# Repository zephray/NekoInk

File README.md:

NekoInk
=======

**This project has been superseded by [Glider](https://gitlab.com/zephray/glider) and will not be updated further.**

NekoInk is an open-source, programmable, and versatile E-paper display platform. It offers connectivity options to various type of E-paper screens, and flexible programming environment choices.

# Hardware

## Mainboard

The 1st generation of NekoInk has the following specs:

* Processing
    - NXP i.MX6ULL, 900 MHz Cortex-A7 processor
    - 512 MB DDR3L-1066 memory
* Display
    - Support for EPD screens from 6" to 13.3"
    - Up to 32 greyscale levels / 32768 colors (depends on screen)
    - 40 pin connector for ED103TC1/ES103TC2/GDEW101C01
    - 6 and 12 pin connector for capacitive touch screen (shared signal)
    - 30 pin connector for LVDS LCDs
* Connectivity
    - MicroSD slot for storage
    - 1x USB Micro-B for USB Device and charging
    - 1x USB Micro-AB for USB Host
    - 1x USB Micro-B for USB Serial terminal
    - 1x DVP port for HDMI input or camera module
    - Integrated WiFi and Bluetooth
* Power
    - AXP209 PMIC with Lithium battery charger and coulomb counter
    - Power consumption T.B.D.

## Screen Adapter

Adapter boards are available in this repo to adapt the following screens:

* 39 pin connector for ED060SC4/ED133UT2
* 34 pin connector for ED060SCF/SCN/SCP/XC3/XC5/XC9/XD4/XD6/XH2/KC1/KD1
* 35 pin connector for ED060XC8/TC1
* 50 pin connector for ES108FC1

It's possible to use a simple FPC extender to support the following screens:

* ED078KC1/KH4/GDEW078M01/078C01

The hardware is designed with KiCAD 7.0.

## Status

The 1st gen mainboard is finished, soldered, and tested and considered stable. However there is no plan for mass-production.

# Software

T.B.D.

## Operating System

Linux T.B.D.

## Waveform

This project uses a human-readable waveform format (iwf, Interchangable Waveform Format) described below. Currently this could be converted into .fw format used by i.MX6/7 EPDC/EPDCv2. Converting from Eink's wbf format is also supported.

### Waveform Format

The waveform consists of one descriptor file in iwf extension (ini format) and various lut data files in csv format.

The descriptor contains the follwoing required fields:

* VERISON: the version of the descriptor
* NAME: (optional) original name for the waveform
* BPP: (optional, default 4) 4 or 5, representing the internal state count used for waveform
* PREFIX: the filename prefix for actual waveform files
* MODES: the total modes supported by the waveform
* TEMPS: the total number of temperature ranges supported by the waveform
* T*x*RANGE: the supported temperature in degC, where x is the temperature ID
* TUPBOUND: (optional) upper bound for temperature range, each range is T*x*RANGE to T*x+1*RANGE (or TUPBOUND in case of the last one)

In v2.0, the following fields are added:

* TABLES: total number of LUTs inside the waveform
* TB*x*FC: the frame count for the table, where x is the table ID

In v1.0, table are directly addressed and stored by its mode and temperature ID (expect things like PREFIX_M1_T2.csv for mode 1 and temperature range 2). In v2.0, tables are indirectly addressed and stored (expect things like PREFIX_TB2.csv for the second table, and one or more mode/temperature combination to use/ reference table 2).

Each mode has its own mode section named \[MODE*x*\], where x is the mode ID, containing the following fields:

* NAME: the name for that mode
* TxFC: the frame count for the temperature in that mode, where x is the temperature ID (v1.0 only)
* T*TABLE: the table used for the temperature in that mode (v2.0 only)

There should be a number of LUTs, saved in the filename of either PREFIX_M*x*_T*y*.csv (v1.0) or PREFIX_TB*x*.csv. Each csv file should contain the a LUT like this: lut\[src\]\[dst\]\[frame\], which means, to transition from src greyscale level to dst greyscale level, at a certain frame in a frame sequence, what voltage should be applied to the screen (0/3: GND / Keep, 1: VNEG / To black, 2: VPOS / To white). Each line contains the frame sequence for one or more source to destination pairs.

For example:

* ```4,7,1,1,1,0,2``` means to transition from greyscale level 4 to greyscale level 7, there should be 5 frames, each applying VNEG VNEG VNEG GND VPOS
* ```0:14:15,2,2,2``` means to transition from any greyscale level from 0 to 14 to greyscale level 15, there should be 3 frames, each applying VPOS VPOS VPOS

These are provided to only illustrate the file format, they are not valid or meaningful Eink driving sequences.

With current design, each mode should have fixed frame count for all associated frame sequences.

### Converting

Tools are provided in utils/ folder.

* To convert from iwf to fw (iMX6/7 EPDC format): ```./mxc_wvfm_asm v1/v2 input.iwf output.fw``` 
* To convert from fw to iwf: ```./mxc_wvfm_dump v1/v2 input.fw output_prefix```
* To convert from wbf to iwf: ```./wbf_wvfm_dump input.wbf output_prefix```

In some cases, the waveform stored on the panel/ controller's flash is compressed. A decompressing tool is also provided that might work.

### Generating

To be implemented.

# License

The design, unless otherwise specified, is released under the CERN Open Source Hardware License version 2 permissive variant, CERN-OHL-P. A copy of the license is provided in the source repository. Additionally, user guide of the license is provided on ohwr.org.

The waveform converting tool is licensed under GNU GPLv2+ due to use of Linux kernel source code and other people's valuable prior work. See each tools' source code for the complete copyright.

The image viewer tool is licensed under MIT. stb library used in the image viewer is public domain.

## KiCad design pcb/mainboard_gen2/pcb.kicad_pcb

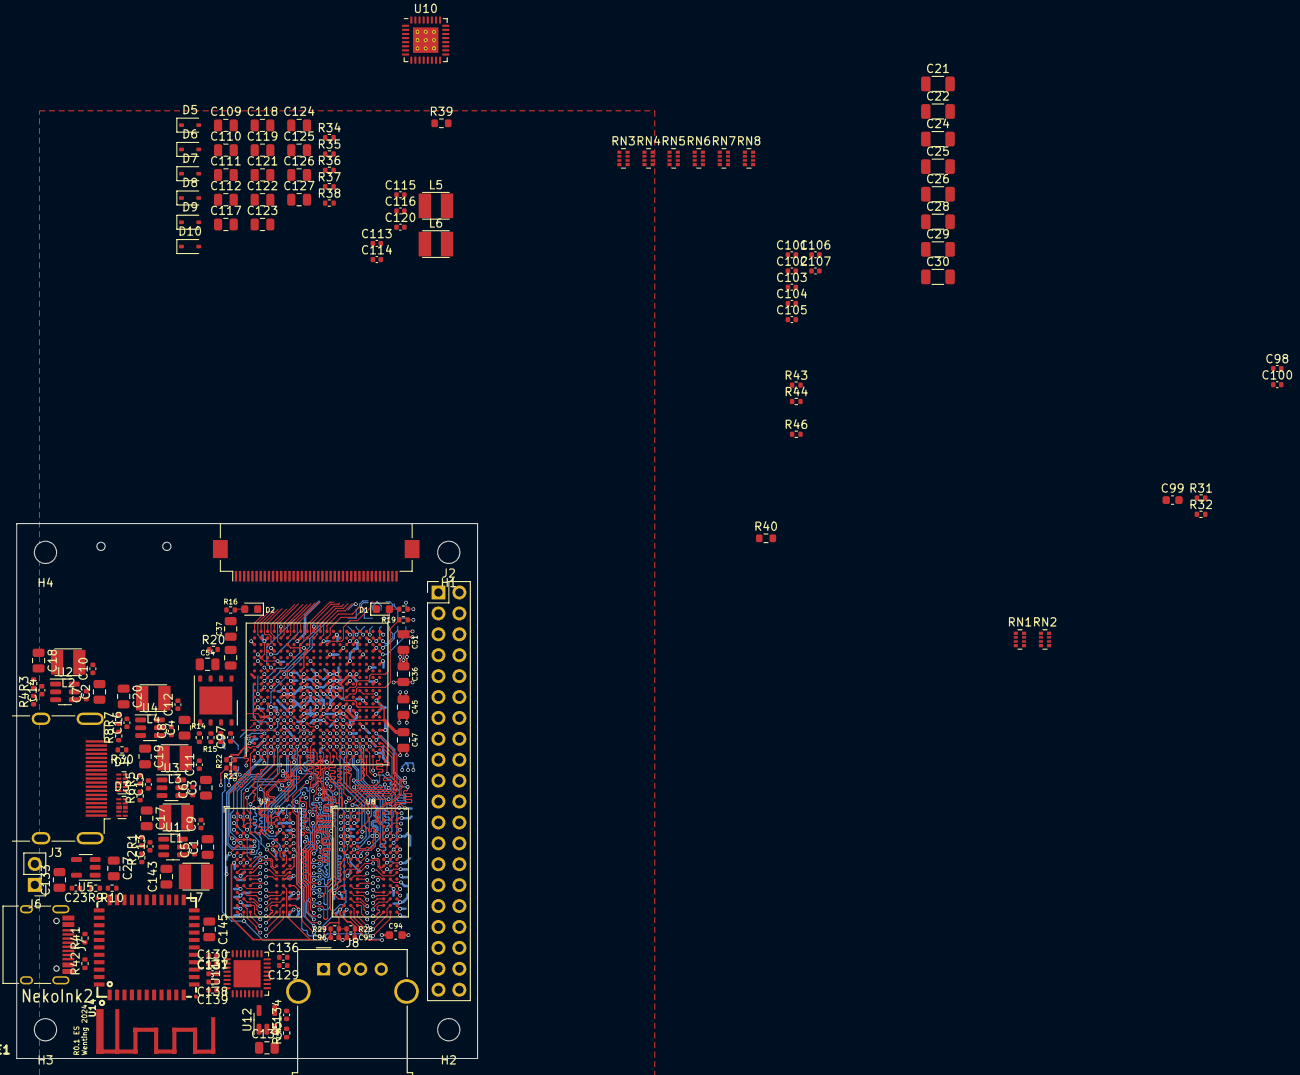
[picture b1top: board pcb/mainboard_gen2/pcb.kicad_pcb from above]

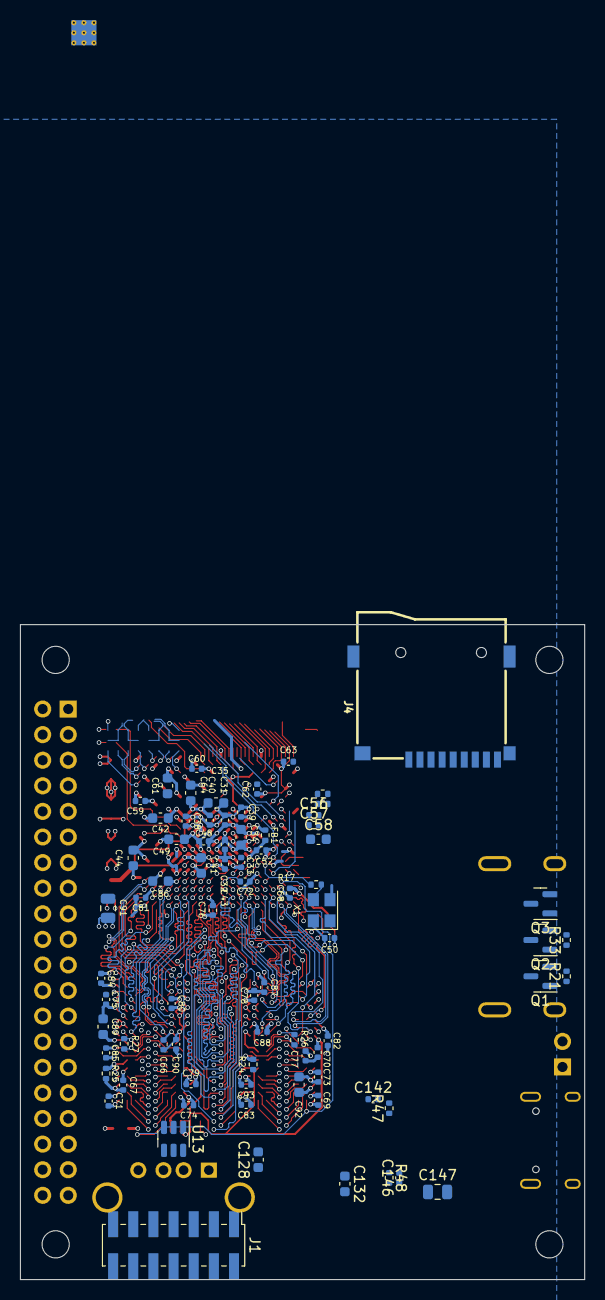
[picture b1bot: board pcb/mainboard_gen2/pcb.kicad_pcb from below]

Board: 6 copper layers, 56.0 x 65.0 mm, 245 parts (77 on the bottom side), 245 nets.

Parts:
AE1: Antenna_Shield; bt_antenna_1ant_2gnd_mirror
C1, C2, C3, C4, C17, C18, C19, C20, C27, C119, C125, C133, C135, C143, C145, C147: 10uF; C_0805_2012Metric
C5, C6, C7, C8, C9, C10, C11, C12, C23, C67, C70, C95, C96, C100, C113, C114, C115, C129, C130, C131, C134, C136, C137, C138, C139, C142, C146: 100nF; C_0402_1005Metric
C13, C14, C15, C16: 47pF; C_0402_1005Metric
C21, C22, C24, C25, C26, C28, C29, C30: 47uF/10V; C_1206_3216Metric
C31, C32, C33, C38, C39, C40, C43, C48, C50, C52, C56, C57, C59, C60, C62, C63, C68, C72, C76, C81, C97: 470nF; C_0402_1005Metric
C34, C35, C41, C42, C44, C49, C58, C61, C64, C86, C94, C128, C132: 4.7uF; C_0603_1608Metric
C36, C37, C45, C46, C47, C51: 100uF; C_0805_2012Metric
C54, C91: 47uF; C_0805_2012Metric
C66, C69, C71, C73, C74, C75, C77, C78, C79, C80, C82, C83, C84, C85, C87, C88, C90, C93, C101, C102, C103, C104, C105, C106, C107: 220nF; C_0402_1005Metric
C89, C92, C99: 22uF; C_0603_1608Metric
C98: 18pF; C_0402_1005Metric
C109, C110, C111, C112: 1uF/25V; C_0805_2012Metric
C116: 1uF; C_0402_1005Metric
C117, C118, C121, C122, C123, C124, C126, C127: 4.7uF/25V; C_0805_2012Metric
C120: 2.2nF; C_0402_1005Metric
D1, D2: LED; LED_0603_1608Metric
D3, D4: RCLAMP0524P; Diodes_UDFN-10_1.0x2.5mm_P0.5mm
D5, D6, D7, D8, D9, D10: B0530WS; D_SOD-323
FB1: 120R; R_0402_1005Metric
H1, H2, H3, H4: MountingHole; MountingHole_2.7mm_M2.5
J1: JTAG; PinHeader_2x07_P2.00mm_Vertical_SMD
J2: GPIO; PinHeader_2x20_P2.54mm_Vertical
J3: HDMI_A; HDMI_A_Molex_208658-1001_Horizontal
J4: MICRO_SD(TFC-WPAPR-08); TFC-WPAPR-08
J5: 0.5mm; Hirose_FH12-40S-0.5SH_1x40-1MP_P0.50mm_Horizontal_Reversed
J6: Conn_01x02; PinHeader_1x02_P2.54mm_Vertical
J7: USB_C_Receptacle_USB2.0; USB_C_Receptacle_HRO_TYPE-C-31-M-12
J8: USB_A; USB_A_Molex_67643_Horizontal
L1, L2, L3, L4, L5, L6, L7: 4.7uH; L_1212
Q1, Q2, Q3: BSS138; SOT-23
R1: 91K/1%; R_0402_1005Metric
R2, R3, R5: 20K/1%; R_0402_1005Metric
R4: 10K/1%; R_0402_1005Metric
R6, R7: 16K/1%; R_0402_1005Metric
R8, R36: 27K/1%; R_0402_1005Metric
R9, R19: 4.7K; R_0402_1005Metric
R10: 16K; R_0402_1005Metric
R11, R12, R13, R14, R15, R31: 20K; R_0402_1005Metric
R16, R18, R30, R46: 1K; R_0402_1005Metric
R17, R32, R43, R47, R48: 22R; R_0402_1005Metric
R20, R21, R33, R41, R42, R45: 10K; R_0402_1005Metric
R22, R23: 80R; R_0402_1005Metric
R24, R25: 240R 1%; R_0402_1005Metric
R26, R27: 100R; R_0402_1005Metric
R28, R29: 1.5K/0.5%; R_0402_1005Metric
R34: 562K/1%; R_0402_1005Metric
R35: 806K/1%; R_0402_1005Metric
R37: 49.9K/1%; R_0402_1005Metric
R38: 10R; R_0402_1005Metric
R39: 0.5R; R_0603_1608Metric
R40: 22R; R_0603_1608Metric
R44: 12K/1%; R_0402_1005Metric
RN1, RN2: 51; R_Array_Convex_4x0402
RN3, RN4, RN5, RN6, RN7, RN8: 33; R_Array_Convex_4x0402
U1, U2, U3, U4: SY8120; TSOT-23-6
U5, U12: MT9700; SOT-23-5
U6: XC7Z010-CLG400; Xilinx_CLG400
U7, U8: MT41K256M16HA; BGA-96_9.0x13.0mm_Layout2x3x16_P0.8mm
U9: W25Q128JVP; WSON-8-1EP_6x5mm_P1.27mm_EP3.4x4mm
U10: MAX17135; QFN-32-1EP_5x5mm_P0.5mm_EP3.1x3.1mm_ThermalVias
U11: USB3300; QFN-32-1EP_5x5mm_P0.5mm_EP3.3x3.3mm
U13: USBLC6-2SC6; SOT-23-6
U14: AP6330(BCM4330); RL-SM02BD(RTL8723BS)
X1: 33.33MHz; Oscillator_SMD_Abracon_ASE-4Pin_3.2x2.5mm

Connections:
+1V0: C16.2, C20.2, C31.1, C33.1, C35.1, C37.1, C38.1, C39.1, C40.1, C41.1, C42.1, C46.1, C47.1, L4.2, R7.2, U6.G7 (VCCPINT[6]), U6.G11 (VCCBRAM[2]), U6.G13 (VCCINT[9]), U6.H10 (VCCBRAM[2]), U6.H12 (VCCINT[9]), U6.J7 (VCCPINT[6]), U6.J13 (VCCINT[9]), U6.K12 (VCCINT[9]), U6.L7 (VCCPINT[6]), U6.L13 (VCCINT[9]), U6.M12 (VCCINT[9]), U6.N7 (VCCPINT[6]), U6.N13 (VCCINT[9]), U6.P8 (VCCPINT[6]), U6.P12 (VCCINT[9]), U6.R7 (VCCPINT[6]), U6.R13 (VCCINT[9])
+1V8: C14.2, C18.2, C32.1, C34.1, C36.1, C48.1, C49.1, C51.1, C59.1, C60.1, C61.1, FB1.2, L2.2, R3.2, U6.F8 (VCCPAUX[5]), U6.F11 (VCCBATT_0), U6.G9 (VCCPAUX[5]), U6.H8 (VCCPAUX[5]), U6.J9 (VCCADC_0), U6.J11 (VCCAUX[6]), U6.K8 (VCCPAUX[5]), U6.L11 (VCCAUX[6]), U6.M8 (VCCPAUX[5]), U6.N9 (VCCAUX[6]), U6.N11 (VCCAUX[6]), U6.N19 (VCCO_34[6]), U6.P10 (VCCAUX[6]), U6.R9 (VCCAUX[6]), U6.R15 (VCCO_34[6]), U6.T18 (VCCO_34[6]), U6.V14 (VCCO_34[6]), U6.W17 (VCCO_34[6]), U6.Y20 (VCCO_34[6])
+1V35: C15.2, C19.2, C66.1, C68.1, C69.1, C71.1, C72.1, C73.1, C74.1, C75.1, C76.1, C77.1, C78.1, C79.1, C80.1, C81.1, C82.1, C83.1, C84.1, C85.1, C86.1, C87.1, C88.1, C89.1, C90.1, C91.1, C92.1, C93.1, C94.1, C95.1, L3.2, R5.2, R22.1, R28.1, U6.A3 (VCCO_DDR_502[10]), U6.D2 (VCCO_DDR_502[10]), U6.E5 (VCCO_DDR_502[10]), U6.G1 (VCCO_DDR_502[10]), U6.H4 (VCCO_DDR_502[10]), U6.L3 (VCCO_DDR_502[10]), U6.P2 (VCCO_DDR_502[10]), U6.R5 (VCCO_DDR_502[10]), U6.U1 (VCCO_DDR_502[10]), U6.V4 (VCCO_DDR_502[10]), U7.A1 (VDDQ), U7.A8 (VDDQ), U7.B2 (VDD), U7.C1 (VDDQ), U7.C9 (VDDQ), U7.D2 (VDDQ), U7.D9 (VDD), U7.E9 (VDDQ), U7.F1 (VDDQ), U7.G7 (VDD), U7.H2 (VDDQ), U7.H9 (VDDQ), U7.K2 (VDD), U7.K8 (VDD), U7.N1 (VDD), U7.N9 (VDD), U7.R1 (VDD), U7.R9 (VDD), U8.A1 (VDDQ), U8.A8 (VDDQ), U8.B2 (VDD), U8.C1 (VDDQ), U8.C9 (VDDQ), U8.D2 (VDDQ), U8.D9 (VDD), U8.E9 (VDDQ), U8.F1 (VDDQ), U8.G7 (VDD), U8.H2 (VDDQ), U8.H9 (VDDQ), U8.K2 (VDD), U8.K8 (VDD), U8.N1 (VDD), U8.N9 (VDD), U8.R1 (VDD), U8.R9 (VDD)
+3V3: C13.2, C17.2, C43.2, C44.2, C45.2, C50.2, C56.1, C57.1, C58.1, C62.1, C63.1, C64.1, C97.2, C99.1, C100.1, C105.1, C136.1, C137.1, C138.1, C139.1, C142.1, C145.1, C146.1, C147.1, J1.2, J2.1, J2.17, J4.4 (VDD), J5.5, J5.11, L1.2, Q1.1 (G), Q2.1 (G), Q3.1 (G), R1.2, R11.1, R14.1, R18.1, R19.1, R20.1, R21.1, R31.1, R33.1, RN1.1 (R1.1), RN1.2 (R2.1), RN1.3 (R3.1), RN1.4 (R4.1), RN2.1 (R1.1), RN2.2 (R2.1), RN2.3 (R3.1), RN2.4 (R4.1), U6.A13 (VCCO_MIO1_501[4]), U6.B6 (VCCO_MIO0_500[2]), U6.B16 (VCCO_MIO1_501[4]), U6.C19 (VCCO_35[6]), U6.D7 (VCCO_MIO0_500[2]), U6.D12 (VCCO_MIO1_501[4]), U6.E15 (VCCO_MIO1_501[4]), U6.F18 (VCCO_35[6]), U6.H14 (VCCO_35[6]), U6.J17 (VCCO_35[6]), U6.K6 (VCCO_0), U6.K20 (VCCO_35[6]), U6.M6 (CFGBVS_0), U6.M16 (VCCO_35[6]), U6.N6 (RSVDVCC3), U6.R6 (RSVDVCC2), U6.T6 (RSVDVCC1), U6.T8 (VCCO_13[4]), U6.U11 (VCCO_13[4]), U6.W7 (VCCO_13[4]), U6.Y10 (VCCO_13[4]), U9.8 (VCC), U10.11 (VDD), U11.6 (VDD3.3), U11.16 (VDD3.3), U11.25 (VDD3.3), U11.30 (VDD3.3), U11.31 (REG_EN), U14.6 (BT_WAKE), U14.9 (VBAT), U14.22 (VDD_IO), X1.1 (EN), X1.4 (Vdd)
+5V: C1.2, C2.2, C3.2, C4.2, C5.2, C6.2, C7.2, C8.2, C21.2, C22.2, C24.2, C25.2, C26.2, C27.2, C28.2, C29.2, C30.2, J2.2, J2.4, R30.1, U1.4 (~SHDN), U1.5 (IN), U2.4 (~SHDN), U2.5 (IN), U3.4 (~SHDN), U3.5 (IN), U4.4 (~SHDN), U4.5 (IN), U5.1 (VOUT)
+DRAM_VREF: C67.1, C70.1, C95.2, C96.1, R28.2, R29.1, U6.H6 (PS_DDR_VREF0_502), U6.P6 (PS_DDR_VREF1_502), U7.H1 (VrefDQ), U7.M8 (VrefCA), U8.H1 (VrefDQ), U8.M8 (VrefCA)
/connector/HPD_5V: J3.19 (HPD), Q3.3 (D), R30.2
/connector/SCL_5V: J3.15 (SCL), Q1.3 (D)
/connector/SDA_5V: J3.16 (SDA), Q2.3 (D)
/cpu/FPGA_INIT_B: R19.2, U6.R10 (INIT_B_0)
/cpu/LED: R16.1, U6.E6 (PS_MIO0_500)
/cpu/PS_CLK: R17.2, U6.E7 (PS_CLK_500)
/cpu/VCCPLL: C52.2, C54.2, FB1.1, U6.G8 (VCCPLL)
/ddr/DRAM_ADDR0: U6.N2 (PS_DDR_A0_502), U7.N3 (A0), U8.N3 (A0)
/ddr/DRAM_ADDR1: U6.K2 (PS_DDR_A1_502), U7.P7 (A1), U8.P7 (A1)
/ddr/DRAM_ADDR2: U6.M3 (PS_DDR_A2_502), U7.P3 (A2), U8.P3 (A2)
/ddr/DRAM_ADDR3: U6.K3 (PS_DDR_A3_502), U7.N2 (A3), U8.N2 (A3)
/ddr/DRAM_ADDR4: U6.M4 (PS_DDR_A4_502), U7.P8 (A4), U8.P8 (A4)
/ddr/DRAM_ADDR5: U6.L1 (PS_DDR_A5_502), U7.P2 (A5), U8.P2 (A5)
/ddr/DRAM_ADDR6: U6.L4 (PS_DDR_A6_502), U7.R8 (A6), U8.R8 (A6)
/ddr/DRAM_ADDR7: U6.K4 (PS_DDR_A7_502), U7.R2 (A7), U8.R2 (A7)
/ddr/DRAM_ADDR8: U6.K1 (PS_DDR_A8_502), U7.T8 (A8), U8.T8 (A8)
/ddr/DRAM_ADDR9: U6.J4 (PS_DDR_A9_502), U7.R3 (A9), U8.R3 (A9)
/ddr/DRAM_ADDR10: U6.F5 (PS_DDR_A10_502), U7.L7 (A10), U8.L7 (A10)
/ddr/DRAM_ADDR11: U6.G4 (PS_DDR_A11_502), U7.R7 (A11), U8.R7 (A11)
/ddr/DRAM_ADDR12: U6.E4 (PS_DDR_A12_502), U7.N7 (A12/~BC), U8.N7 (A12/~BC)
/ddr/DRAM_ADDR13: U6.D4 (PS_DDR_A13_502), U7.T3 (A13), U8.T3 (A13)
/ddr/DRAM_ADDR14: U6.F4 (PS_DDR_A14_502), U7.T7 (A14/NC), U8.T7 (A14/NC)
/ddr/DRAM_BA0: U6.L5 (PS_DDR_BA0_502), U7.M2 (BA0), U8.M2 (BA0)
/ddr/DRAM_BA1: U6.R4 (PS_DDR_BA1_502), U7.N8 (BA1), U8.N8 (BA1)
/ddr/DRAM_BA2: U6.J5 (PS_DDR_BA2_502), U7.M3 (BA2), U8.M3 (BA2)
/ddr/DRAM_CASB: U6.P5 (PS_DDR_CAS_B_502), U7.K3 (~CAS), U8.K3 (~CAS)
/ddr/DRAM_CKE: U6.N3 (PS_DDR_CKE_502), U7.K9 (CKE), U8.K9 (CKE)
/ddr/DRAM_CKN: R26.2, R27.2, U6.M2 (PS_DDR_CKN_502), U7.K7 (~CK), U8.K7 (~CK)
/ddr/DRAM_CKP: R26.1, R27.1, U6.L2 (PS_DDR_CKP_502), U7.J7 (CK), U8.J7 (CK)
/ddr/DRAM_CSB: U6.N1 (PS_DDR_CS_B_502), U7.L2 (~CS), U8.L2 (~CS)
/ddr/DRAM_DATA0: U6.C3 (PS_DDR_DQ0_502), U7.E3 (DQ0)
/ddr/DRAM_DATA1: U6.B3 (PS_DDR_DQ1_502), U7.F7 (DQ1)
/ddr/DRAM_DATA2: U6.A2 (PS_DDR_DQ2_502), U7.F2 (DQ2)
/ddr/DRAM_DATA3: U6.A4 (PS_DDR_DQ3_502), U7.F8 (DQ3)
/ddr/DRAM_DATA4: U6.D3 (PS_DDR_DQ4_502), U7.H3 (DQ4)
/ddr/DRAM_DATA5: U6.D1 (PS_DDR_DQ5_502), U7.H8 (DQ5)
/ddr/DRAM_DATA6: U6.C1 (PS_DDR_DQ6_502), U7.G2 (DQ6)
/ddr/DRAM_DATA7: U6.E1 (PS_DDR_DQ7_502), U7.H7 (DQ7)
/ddr/DRAM_DATA8: U6.E2 (PS_DDR_DQ8_502), U7.D7 (DQ8)
/ddr/DRAM_DATA9: U6.E3 (PS_DDR_DQ9_502), U7.C3 (DQ9)
/ddr/DRAM_DATA10: U6.G3 (PS_DDR_DQ10_502), U7.C8 (DQ10)
/ddr/DRAM_DATA11: U6.H3 (PS_DDR_DQ11_502), U7.C2 (DQ11)
/ddr/DRAM_DATA12: U6.J3 (PS_DDR_DQ12_502), U7.A7 (DQ12)
/ddr/DRAM_DATA13: U6.H2 (PS_DDR_DQ13_502), U7.A2 (DQ13)
/ddr/DRAM_DATA14: U6.H1 (PS_DDR_DQ14_502), U7.B8 (DQ14)
/ddr/DRAM_DATA15: U6.J1 (PS_DDR_DQ15_502), U7.A3 (DQ15)
/ddr/DRAM_DATA16: U6.P1 (PS_DDR_DQ16_502), U8.E3 (DQ0)
/ddr/DRAM_DATA17: U6.P3 (PS_DDR_DQ17_502), U8.F7 (DQ1)
/ddr/DRAM_DATA18: U6.R3 (PS_DDR_DQ18_502), U8.F2 (DQ2)
/ddr/DRAM_DATA19: U6.R1 (PS_DDR_DQ19_502), U8.F8 (DQ3)
/ddr/DRAM_DATA20: U6.T4 (PS_DDR_DQ20_502), U8.H3 (DQ4)
/ddr/DRAM_DATA21: U6.U4 (PS_DDR_DQ21_502), U8.H8 (DQ5)
/ddr/DRAM_DATA22: U6.U2 (PS_DDR_DQ22_502), U8.G2 (DQ6)
/ddr/DRAM_DATA23: U6.U3 (PS_DDR_DQ23_502), U8.H7 (DQ7)
/ddr/DRAM_DATA24: U6.V1 (PS_DDR_DQ24_502), U8.D7 (DQ8)
/ddr/DRAM_DATA25: U6.Y3 (PS_DDR_DQ25_502), U8.C3 (DQ9)
/ddr/DRAM_DATA26: U6.W1 (PS_DDR_DQ26_502), U8.C8 (DQ10)
/ddr/DRAM_DATA27: U6.Y4 (PS_DDR_DQ27_502), U8.C2 (DQ11)
/ddr/DRAM_DATA28: U6.Y2 (PS_DDR_DQ28_502), U8.A7 (DQ12)
/ddr/DRAM_DATA29: U6.W3 (PS_DDR_DQ29_502), U8.A2 (DQ13)
/ddr/DRAM_DATA30: U6.V2 (PS_DDR_DQ30_502), U8.B8 (DQ14)
/ddr/DRAM_DATA31: U6.V3 (PS_DDR_DQ31_502), U8.A3 (DQ15)
/ddr/DRAM_DQM0: U6.A1 (PS_DDR_DM0_502), U7.E7 (LDM)
/ddr/DRAM_DQM1: U6.F1 (PS_DDR_DM1_502), U7.D3 (UDM)
/ddr/DRAM_DQM2: U6.T1 (PS_DDR_DM2_502), U8.E7 (LDM)
/ddr/DRAM_DQM3: U6.Y1 (PS_DDR_DM3_502), U8.D3 (UDM)
/ddr/DRAM_ODT: U6.N5 (PS_DDR_ODT_502), U7.K1 (ODT), U8.K1 (ODT)
/ddr/DRAM_RASB: U6.P4 (PS_DDR_RAS_B_502), U7.J3 (~RAS), U8.J3 (~RAS)
/ddr/DRAM_RST: U6.B4 (PS_DDR_DRST_B_502), U7.T2 (~RESET), U8.T2 (~RESET)
/ddr/DRAM_SDQSN_0: U6.B2 (PS_DDR_DQS_N0_502), U7.G3 (~LDQS)
/ddr/DRAM_SDQSN_1: U6.F2 (PS_DDR_DQS_N1_502), U7.B7 (~UDQS)
/ddr/DRAM_SDQSN_2: U6.T2 (PS_DDR_DQS_N2_502), U8.G3 (~LDQS)
/ddr/DRAM_SDQSN_3: U6.W4 (PS_DDR_DQS_N3_502), U8.B7 (~UDQS)
/ddr/DRAM_SDQSP_0: U6.C2 (PS_DDR_DQS_P0_502), U7.F3 (LDQS)
/ddr/DRAM_SDQSP_1: U6.G2 (PS_DDR_DQS_P1_502), U7.C7 (UDQS)
/ddr/DRAM_SDQSP_2: U6.R2 (PS_DDR_DQS_P2_502), U8.F3 (LDQS)
/ddr/DRAM_SDQSP_3: U6.W5 (PS_DDR_DQS_P3_502), U8.C7 (UDQS)
/ddr/DRAM_WEB: U6.M5 (PS_DDR_WE_B_502), U7.L3 (~WE), U8.L3 (~WE)
/usb/HOST_VBUS: C135.1, J8.1 (VBUS), R46.1, U12.1 (VOUT), U13.5 (VBUS)
/usb/USB_DM: J8.2 (D-), U11.8 (DM), U13.1 (I/O1), U13.6 (I/O1)
/usb/USB_DP: J8.3 (D+), U11.7 (DP), U13.3 (I/O2), U13.4 (I/O2)
BT_SHUTDOWN: U6.F14 (PS_MIO21_501), U14.34 (BT_RST_N)
BT_UART_RXD: U6.B18 (PS_MIO18_501), U14.42 (UART_TXD)
BT_UART_TXD: U6.D10 (PS_MIO19_501), U14.43 (UART_RXD)
DDC_SCL: Q1.2 (S), R21.2, U6.J14 (IO_L20N_T3_AD6N_35)
DDC_SDA: Q2.2 (S), R33.2, U6.N16 (IO_L21N_T3_DQS_AD14N_35)
EPDC_D0: RN4.6 (R3.2), U6.F16 (IO_L6P_T0_35)
EPDC_D1: RN4.7 (R2.2), U6.F17 (IO_L6N_T0_VREF_35)
EPDC_D2: RN4.8 (R1.2), U6.M19 (IO_L7P_T1_AD2P_35)
EPDC_D3: RN5.5 (R4.2), U6.M20 (IO_L7N_T1_AD2N_35)
EPDC_D4: RN5.6 (R3.2), U6.M17 (IO_L8P_T1_AD10P_35)
EPDC_D5: RN5.7 (R2.2), U6.L20 (IO_L9N_T1_DQS_AD3N_35)
EPDC_D6: RN5.8 (R1.2), U6.L19 (IO_L9P_T1_DQS_AD3P_35)
EPDC_D7: RN6.5 (R4.2), U6.J19 (IO_L10N_T1_AD11N_35)
EPDC_D8: RN6.6 (R3.2), U6.K19 (IO_L10P_T1_AD11P_35)
EPDC_D9: RN6.7 (R2.2), U6.B19 (IO_L2P_T0_AD8P_35)
EPDC_D10: RN6.8 (R1.2), U6.B20 (IO_L1N_T0_AD0N_35)
EPDC_D11: RN7.5 (R4.2), U6.A20 (IO_L2N_T0_AD8N_35)
EPDC_D12: RN7.6 (R3.2), U6.E18 (IO_L5P_T0_AD9P_35)
EPDC_D13: RN7.7 (R2.2), U6.D20 (IO_L4N_T0_35)
EPDC_D14: RN7.8 (R1.2), U6.D19 (IO_L4P_T0_35)
EPDC_D15: RN8.5 (R4.2), U6.E17 (IO_L3P_T0_DQS_AD1P_35)
EPDC_GDCLK: RN3.7 (R2.2), U6.J15 (IO_25_35)
EPDC_GDOE: RN3.6 (R3.2), U6.G14 (IO_0_35)
EPDC_GDSP: RN3.8 (R1.2), U6.C20 (IO_L1P_T0_AD0P_35)
EPDC_SDCE0: RN8.6 (R3.2), U6.E19 (IO_L5N_T0_AD9N_35)
EPDC_SDCLK: RN4.5 (R4.2), U6.D18 (IO_L3N_T0_DQS_AD1N_35)
EPDC_SDLE: RN8.7 (R2.2), U6.L17 (IO_L11N_T1_SRCC_35)
EPDC_SDOE: RN8.8 (R1.2), U6.M18 (IO_L8N_T1_AD10N_35)
FPGA_DONE: D1.2 (A), Q3.2 (S), R18.2, U6.L15 (IO_L22N_T3_AD7N_35), U6.R11 (DONE_0)
FPGA_TCK: J1.6, U6.F9 (TCK_0)
FPGA_TDI: J1.10, U6.G6 (TDI_0)
FPGA_TDO: J1.8, U6.F6 (TDO_0)
FPGA_TMS: J1.4, U6.J6 (TMS_0)
GND: AE1.2 (Shield), C1.1, C2.1, C3.1, C4.1, C5.1, C6.1, C7.1, C8.1, C17.1, C18.1, C19.1, C20.1, C21.1, C22.1, C23.1, C24.1, C25.1, C26.1, C27.1, C28.1, C29.1, C30.1, C31.2, C32.2, C33.2, C34.2, C35.2, C36.2, C37.2, C38.2, C39.2, C40.2, C41.2, C42.2, C43.1, C44.1, C45.1, C46.2, C47.2, C48.2, C49.2, C50.1, C51.2, C52.1, C54.1, C56.2, C57.2, C58.2, C59.2, C60.2, C61.2, C62.2, C63.2, C64.2, C66.2, C67.2, C68.2, C69.2, C70.2, C71.2, C72.2, C73.2, C74.2, C75.2, C76.2, C77.2, C78.2, C79.2, C80.2, C81.2, C82.2, C83.2, C84.2, C85.2, C86.2, C87.2, C88.2, C89.2, C90.2, C91.2, C92.2, C93.2, C94.2, C96.2, C97.1, C98.2, C99.2, C100.2, C101.2, C102.2, C103.2, C104.2, C105.2, C106.2, C107.2, C115.1, C116.1, C128.2, C129.1, C130.1, C131.1, C132.2, C133.2, C134.1, C135.2, C136.2, C137.2, C138.2, C139.2, C142.2, C143.2, C145.2, C146.2, C147.2, D1.1 (K), D2.1 (K), D3.3 (GND), D3.8 (GND), D4.3 (GND), D4.8 (GND), J1.3, J1.5, J1.7, J1.9, J1.11, J1.13, J2.6, J2.9, J2.14, J2.20, J2.25, J2.30, J2.34, J2.39, J3.2 (D2S), J3.5 (D1S), J3.8 (D0S), J3.11 (CKS), J3.17 (GND), J3.SH, J4.6 (VSS), J4.10, J4.11, J4.12, J4.13, J5.9, J5.12, J5.22, J5.MP (MountPin), J7.A1 (GND), J7.A12 (GND), J7.B1 (GND), J7.B12 (GND), J7.S1 (SHIELD), J8.4 (GND), J8.5 (Shield), R2.1, R4.1, R6.1, R8.1, R9.1, R10.1, R12.1, R13.1, R15.1, R23.1, R24.1, R25.1, R29.2, R36.1, R41.1, R42.1, R44.1, R45.1, U1.2 (GND), U2.2 (GND), U3.2 (GND), U4.2 (GND), U5.2 (GND), U6.A8 (GND[59]), U6.A18 (GND[59]), U6.B1 (GND[59]), U6.B11 (GND[59]), U6.C4 (GND[59]), U6.C9 (GND[59]), U6.C14 (GND[59]), U6.D5 (PS_MIO8_500), U6.D8 (PS_MIO7_500), U6.D17 (GND[59]), U6.E10 (GND[59]), U6.E20 (GND[59]), U6.F3 (GND[59]), U6.F7 (GND[59]), U6.F10 (RSVDGND), U6.G10 (GND[59]), U6.G12 (GND[59]), U6.G16 (GND[59]), U6.H7 (GND[59]), U6.H9 (GND[59]), U6.H11 (GND[59]), U6.H13 (GND[59]), U6.H19 (GND[59]), U6.J2 (GND[59]), U6.J8 (GND[59]), U6.J10 (GNDADC_0), U6.J12 (GND[59]), U6.K5 (GND[59]), U6.K7 (GND[59]), U6.K10 (VREFN_0), U6.K11 (GND[59]), U6.K13 (GND[59]), U6.K15 (GND[59]), U6.L8 (GND[59]), U6.L9 (VREFP_0), U6.L12 (GND[59]), U6.L18 (GND[59]), U6.M1 (GND[59]), U6.M7 (GND[59]), U6.M11 (GND[59]), U6.M13 (GND[59]), U6.N4 (GND[59]), U6.N8 (GND[59]), U6.N10 (GND[59]), U6.N12 (GND[59]), U6.N14 (GND[59]), U6.P7 (GND[59]), U6.P9 (GND[59]), U6.P11 (GND[59]), U6.P13 (GND[59]), U6.P17 (GND[59]), U6.R8 (GND[59]), U6.R12 (GND[59]), U6.R20 (GND[59]), U6.T3 (GND[59]), U6.T7 (GND[59]), U6.T13 (GND[59]), U6.U6 (GND[59]), U6.U16 (GND[59]), U6.V9 (GND[59]), U6.V19 (GND[59]), U6.W2 (GND[59]), U6.W12 (GND[59]), U6.Y5 (GND[59]), U6.Y15 (GND[59]), U7.A9 (VSS), U7.B1 (VSSQ), U7.B3 (VSS), U7.B9 (VSSQ), U7.D1 (VSSQ), U7.D8 (VSSQ), U7.E1 (VSS), U7.E2 (VSSQ), U7.E8 (VSSQ), U7.F9 (VSSQ), U7.G1 (VSSQ), U7.G8 (VSS), U7.G9 (VSSQ), U7.J2 (VSS), U7.J8 (VSS), U7.M1 (VSS), U7.M9 (VSS), U7.P1 (VSS), U7.P9 (VSS), U7.T1 (VSS), U7.T9 (VSS), U8.A9 (VSS), U8.B1 (VSSQ), U8.B3 (VSS), U8.B9 (VSSQ), U8.D1 (VSSQ), U8.D8 (VSSQ), U8.E1 (VSS), U8.E2 (VSSQ), U8.E8 (VSSQ), U8.F9 (VSSQ), U8.G1 (VSSQ), U8.G8 (VSS), U8.G9 (VSSQ), U8.J2 (VSS), U8.J8 (VSS), U8.M1 (VSS), U8.M9 (VSS), U8.P1 (VSS), U8.P9 (VSS), U8.T1 (VSS), U8.T9 (VSS), U9.4 (GND), U9.9 (EP), U10.21 (GND), U10.31 (FBP), U10.33 (EP), U11.1 (GND), U11.2 (GND), U11.5 (ID), U11.9 (RESET), U11.33 (GND), U12.2 (GND), U13.2 (GND), U14.1 (GND), U14.3 (GND), U14.20 (GND), U14.31 (GND), U14.33 (GND), U14.36 (GND), U14.44 (UART_CTS), X1.2 (GND)
GNDPWR: C109.1, C110.2, C111.1, C112.1, C117.1, C118.1, C119.1, C121.1, C122.1, C123.1, C124.1, C125.1, C126.1, C127.1, L5.2, U10.30 (PGND)
IPSOUT: C119.2, C125.2, L6.1, R38.2, U10.27 (INN)
unnamed: AE1.1 (A), U14.2 (WIFI/BT_ANT)
unnamed: C128.1, C129.2, C130.2, U11.15 (VDD1.8), U11.26 (VDD1.8)
unnamed: D2.2 (A), R16.2
unnamed: C114.1, D5.1 (K), D8.2 (A)
unnamed: C110.1, D6.2 (A), U10.2 (PGVDD)
unnamed: C113.1, D6.1 (K), D7.2 (A)
unnamed: C112.2, D8.1 (K), U10.9 (PGVEE)
unnamed: C124.2, C127.2, D9.2 (A), R39.1
unnamed: D9.1 (K), L5.1, U10.26 (LXN)
unnamed: D10.2 (A), L6.2, U10.29 (LXP)
unnamed: C126.2, D10.1 (K), U10.28 (HVINP)
unnamed: C98.1, J4.5 (CLK/SCLK), R32.1
unnamed: J5.6, RN3.3 (R3.1)
unnamed: J5.7, RN3.2 (R2.1)
unnamed: J5.8, RN3.1 (R1.1)
unnamed: J5.13, RN4.4 (R4.1)
unnamed: J5.14, RN4.3 (R3.1)
unnamed: J5.15, RN4.2 (R2.1)
unnamed: J5.16, RN4.1 (R1.1)
unnamed: J5.17, RN5.4 (R4.1)
unnamed: J5.18, RN5.3 (R3.1)
unnamed: J5.19, RN5.2 (R2.1)
unnamed: J5.20, RN5.1 (R1.1)
unnamed: J5.21, RN6.4 (R4.1)
unnamed: J5.23, RN6.3 (R3.1)
unnamed: J5.24, RN6.2 (R2.1)
unnamed: J5.25, RN6.1 (R1.1)
unnamed: J5.26, RN7.4 (R4.1)
unnamed: J5.27, RN7.3 (R3.1)
unnamed: J5.28, RN7.2 (R2.1)
unnamed: J5.29, RN7.1 (R1.1)
unnamed: J5.30, RN8.4 (R4.1)
unnamed: J5.31, RN8.3 (R3.1)
unnamed: J5.32, RN8.2 (R2.1)
unnamed: J5.33, RN8.1 (R1.1)
unnamed: C23.2, J6.2, U5.4 (EN), U5.5 (VIN)
unnamed: J7.A5 (CC1), R41.2
unnamed: J7.B5 (CC2), R42.2
unnamed: C9.2, U1.1 (BS)
unnamed: C13.1, R1.1, R2.2, U1.3 (FB)
unnamed: C9.1, L1.1, U1.6 (SW)
unnamed: C10.2, U2.1 (BS)
unnamed: C14.1, R3.1, R4.2, U2.3 (FB)
unnamed: C10.1, L2.1, U2.6 (SW)
unnamed: C11.2, U3.1 (BS)
unnamed: C15.1, R5.1, R6.2, U3.3 (FB)
unnamed: C11.1, L3.1, U3.6 (SW)
unnamed: C12.2, U4.1 (BS)
unnamed: C16.1, R7.1, R8.2, U4.3 (FB)
unnamed: C12.1, L4.1, U4.6 (SW)
unnamed: R9.2, R10.2, U5.3 (SET)
unnamed: R22.2, U6.G5 (PS_DDR_VRN_502)
unnamed: R23.2, U6.H5 (PS_DDR_VRP_502)
unnamed: R24.2, U7.L8 (ZQ)
unnamed: R25.2, U8.L8 (ZQ)
unnamed: C114.2, U10.10 (DN)
unnamed: C113.2, U10.1 (DP)
unnamed: C120.1, U10.15 (DXN)
unnamed: C120.2, U10.14 (DXP)
unnamed: R35.2, R37.2, U10.8 (FBNG)
unnamed: R34.2, R36.2, U10.3 (FBPG)
unnamed: C123.2, R39.2, U10.25 (HVINN)
unnamed: C116.2, R38.1, U10.32 (IN)
unnamed: C115.2, R37.1, U10.7 (REF)
unnamed: R40.1, U11.14 (CLKOUT)
unnamed: R44.2, U11.32 (RBIAS)
unnamed: R46.2, U11.4 (VBUS)
unnamed: C131.2, C132.1, U11.29 (VDDA1.8)
unnamed: R43.2, U11.28 (XI)
unnamed: R45.2, U12.3 (SET)
unnamed: R47.2, U14.24 (LPO)
unnamed: C143.1, L7.2, U14.23 (VIN_LDO)
unnamed: L7.1, U14.21 (VIN_LDO_OUT)
unnamed: R48.2, U14.10 (XTAL_IN)
unnamed: R17.1, X1.3 (OUT)
PS_SRSTB: J1.14, R20.2, U6.B10 (PS_SRST_B_501)
QSPI_DATA0: R14.2, U6.B8 (PS_MIO2_500), U9.5 (DI(IO0))
QSPI_DATA1: R12.2, U6.D6 (PS_MIO3_500), U9.2 (DO(IO1))
QSPI_DATA2: R13.2, U6.B7 (PS_MIO4_500), U9.3 (IO2)
QSPI_DATA3: R11.2, U6.A6 (PS_MIO5_500), U9.7 (IO3)
QSPI_SCLK: R15.2, U6.A5 (PS_MIO6_500), U9.6 (CLK)
QSPI_SS0: R31.2, U6.A7 (PS_MIO1_500), U9.1 (~CS)
SD0_CLK: R32.2, U6.D14 (PS_MIO40_501)
SD0_CMD: J4.3 (CMD/DI), U6.C17 (PS_MIO41_501)
SD0_DATA0: J4.7 (DAT0/DO), U6.E12 (PS_MIO42_501)
SD0_DATA1: J4.8 (DAT1/RES), U6.A9 (PS_MIO43_501)
SD0_DATA2: J4.1 (DAT2/RES), U6.F13 (PS_MIO44_501)
SD0_DATA3: J4.2 (CD/DAT3/CS), U6.B15 (PS_MIO45_501)
SD0_DET: J4.9, U6.B14 (PS_MIO47_501)
SD1_CLK: U6.D9 (PS_MIO12_500), U14.17 (SD_CLK)
SD1_CMD: U6.C6 (PS_MIO11_500), U14.16 (SD_CMD)
SD1_DATA0: U6.E9 (PS_MIO10_500), U14.18 (SD_D0)
SD1_DATA1: U6.E8 (PS_MIO13_500), U14.19 (SD_D1)
SD1_DATA2: U6.C5 (PS_MIO14_500), U14.14 (SD_D2)
SD1_DATA3: U6.C8 (PS_MIO15_500), U14.15 (SD_D3)
TMDS_CKN: D4.1 (IO1), D4.10 (NC4), J3.12 (CK-), RN2.8 (R1.2), U6.H17 (IO_L13N_T2_MRCC_35)
TMDS_CKP: D4.2 (IO2), D4.9 (NC3), J3.10 (CK+), RN2.7 (R2.2), U6.H16 (IO_L13P_T2_MRCC_35)
TMDS_D0N: D4.4 (IO3), D4.7 (NC2), J3.9 (D0-), RN2.6 (R3.2), U6.G20 (IO_L18N_T2_AD13N_35)
TMDS_D0P: D4.5 (IO4), D4.6 (NC1), J3.7 (D0+), RN2.5 (R4.2), U6.G19 (IO_L18P_T2_AD13P_35)
TMDS_D1N: D3.1 (IO1), D3.10 (NC4), J3.6 (D1-), RN1.8 (R1.2), U6.G18 (IO_L16N_T2_35)
TMDS_D1P: D3.2 (IO2), D3.9 (NC3), J3.4 (D1+), RN1.7 (R2.2), U6.G17 (IO_L16P_T2_35)
TMDS_D2N: D3.4 (IO3), D3.7 (NC2), J3.3 (D2-), RN1.6 (R3.2), U6.H18 (IO_L14N_T2_AD4N_SRCC_35)
TMDS_D2P: D3.5 (IO4), D3.6 (NC1), J3.1 (D2+), RN1.5 (R4.2), U6.J18 (IO_L14P_T2_AD4P_SRCC_35)
USB0_CLKOUT: R40.2, U6.A11 (PS_MIO36_501)
USB0_DATA0: U6.A14 (PS_MIO32_501), U11.24 (DATA0)
USB0_DATA1: U6.D15 (PS_MIO33_501), U11.23 (DATA1)
USB0_DATA2: U6.A12 (PS_MIO34_501), U11.22 (DATA2)
USB0_DATA3: U6.F12 (PS_MIO35_501), U11.21 (DATA3)
USB0_DATA4: U6.C16 (PS_MIO28_501), U11.20 (DATA4)
USB0_DATA5: U6.A10 (PS_MIO37_501), U11.19 (DATA5)
USB0_DATA6: U6.E13 (PS_MIO38_501), U11.18 (DATA6)
USB0_DATA7: U6.C18 (PS_MIO39_501), U11.17 (DATA7)
USB0_DIR: U6.C13 (PS_MIO29_501), U11.12 (DIR)
USB0_NXT: U6.E16 (PS_MIO31_501), U11.11 (NXT)
USB0_STP: U6.C15 (PS_MIO30_501), U11.13 (STP)
VBUS: C133.1, C134.2, J6.1, J7.A4 (VBUS), J7.A9 (VBUS), J7.B4 (VBUS), J7.B9 (VBUS), U12.4 (EN), U12.5 (VIN)
VCOM: C101.1, C104.1, J5.10, J5.40, U10.22 (VCOM)
VGH: C106.1, C111.2, D7.1 (K), J5.3, R34.1, U10.4 (DGVDD)
VGL: C107.1, C109.2, D5.2 (A), J5.1, R35.1, U10.6 (DGVEE)
VNEG: C102.1, C118.2, C122.2, J5.38, U10.24 (NEG)
VPOS: C103.1, C117.2, C121.2, J5.36, U10.23 (POS)
WL_PMU_EN: U6.A17 (PS_MIO20_501), U14.12 (WL_REG_ON)

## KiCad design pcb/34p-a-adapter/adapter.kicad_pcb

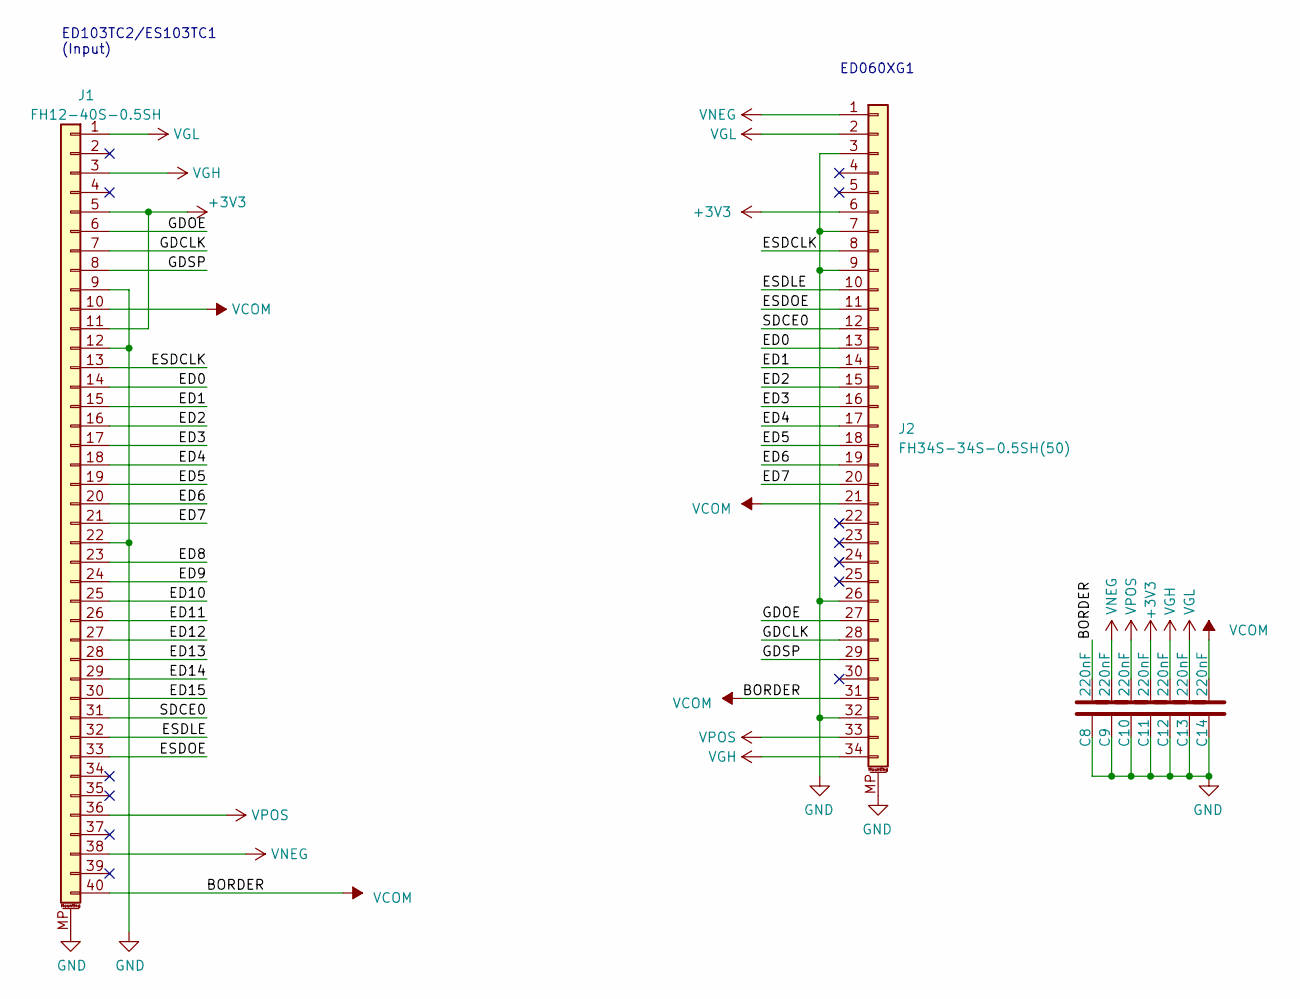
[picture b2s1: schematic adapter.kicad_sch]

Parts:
C8, C9, C10, C11, C12, C13, C14: 220nF; C_0402_1005Metric; LCSC C880414
J1: FH12-40S-0.5SH; Hirose_FH12-40S-0.5SH_1x40-1MP_P0.50mm_Horizontal_Reversed
J2: FH34S-34S-0.5SH(50); Hirose_FH12-34S-0.5SH_1x34-1MP_P0.50mm_Horizontal

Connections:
+3V3: C11.1, J1.5, J1.11, J2.6
/ED0: J1.14, J2.13
/ED1: J1.15, J2.14
/ED2: J1.16, J2.15
/ED3: J1.17, J2.16
/ED4: J1.18, J2.17
/ED5: J1.19, J2.18
/ED6: J1.20, J2.19
/ED7: J1.21, J2.20
/ED8: J1.23
/ED9: J1.24
/ED10: J1.25
/ED11: J1.26
/ED12: J1.27
/ED13: J1.28
/ED14: J1.29
/ED15: J1.30
/ESDCLK: J1.13, J2.8
/ESDLE: J1.32, J2.10
/ESDOE: J1.33, J2.11
/GDCLK: J1.7, J2.28
/GDOE: J1.6, J2.27
/GDSP: J1.8, J2.29
/SDCE0: J1.31, J2.12
GND: C8.2, C9.2, C10.2, C11.2, C12.2, C13.2, C14.2, J1.9, J1.12, J1.22, J1.MP (MountPin), J2.3, J2.7, J2.9, J2.26, J2.32, J2.MP (MountPin)
VCOM: C8.1, C14.1, J1.10, J1.40, J2.21, J2.31
VGH: C12.1, J1.3, J2.34
VGL: C13.1, J1.1, J2.2
VNEG: C9.1, J1.38, J2.1
VPOS: C10.1, J1.36, J2.33

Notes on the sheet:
ED103TC2/ES103TC1 (Input)
ED060XG1

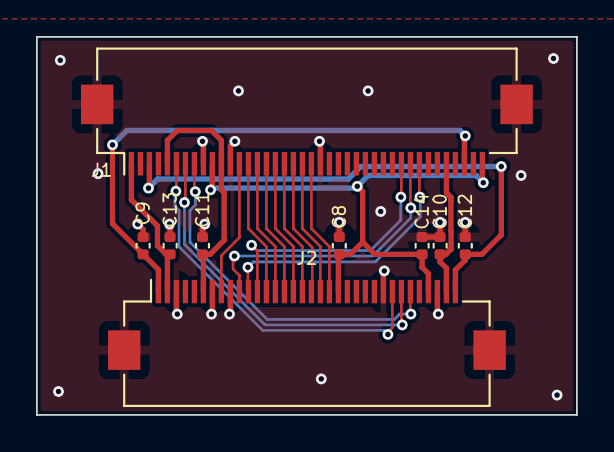
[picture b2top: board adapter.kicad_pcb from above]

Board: 2 copper layers, 30.0 x 21.0 mm, 9 parts (0 on the bottom side), 22 nets.

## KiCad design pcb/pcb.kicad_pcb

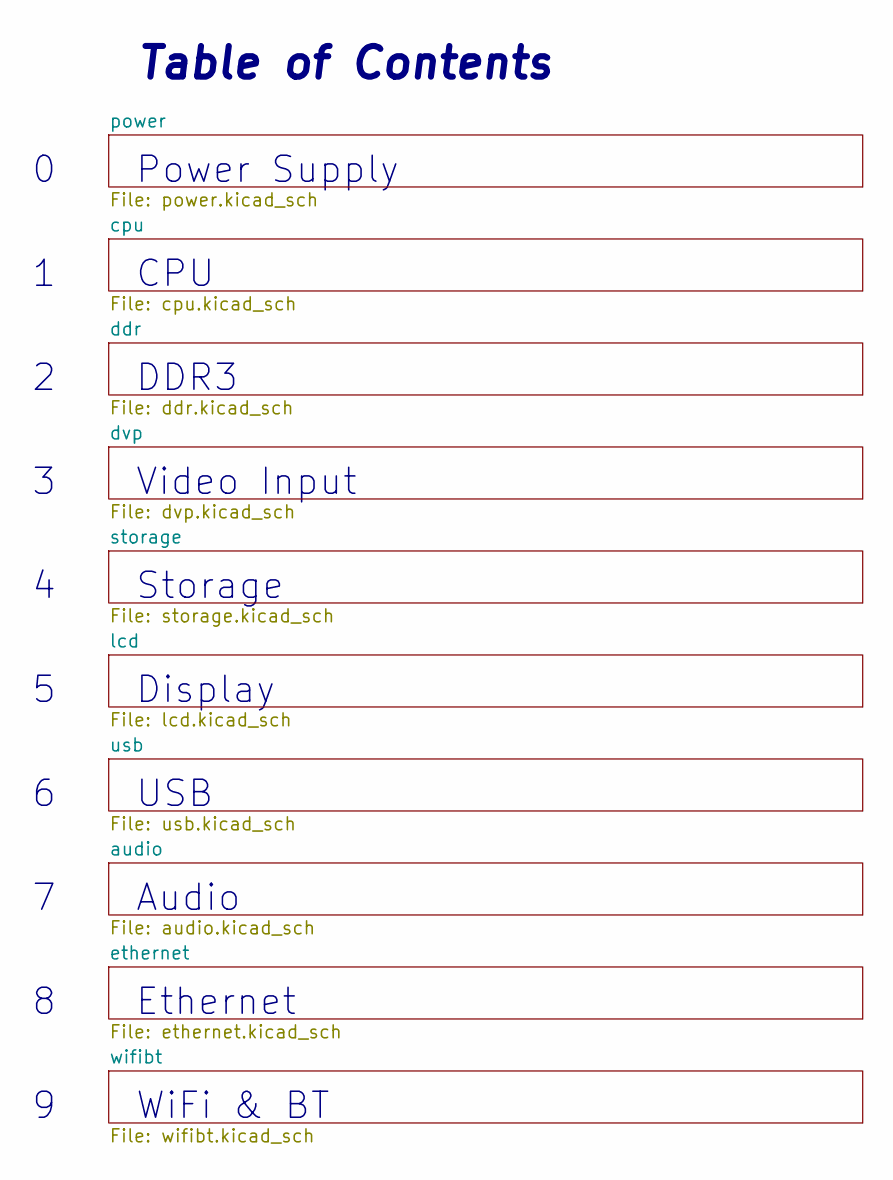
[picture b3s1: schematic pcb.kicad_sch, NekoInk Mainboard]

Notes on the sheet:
Table of Contents
Power Supply
CPU
DDR3
Video Input
Storage
Display
USB
Audio
Ethernet
WiFi & BT

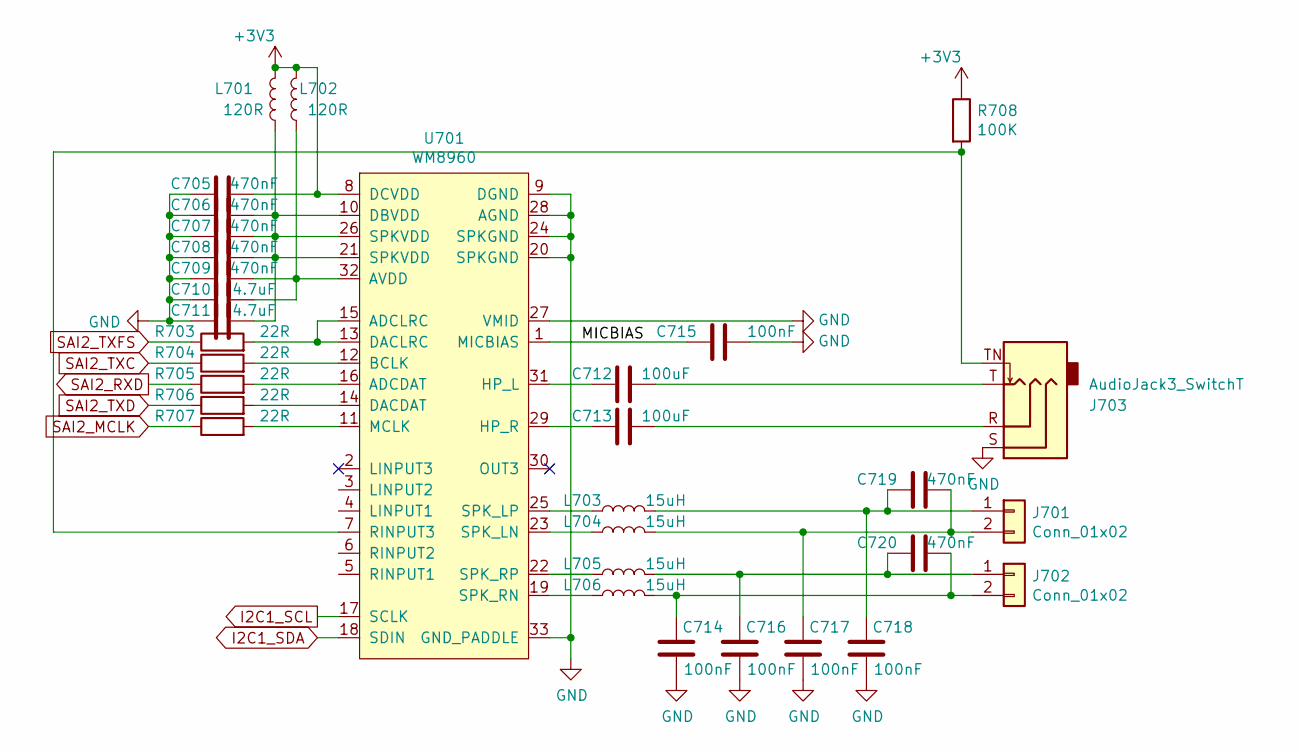
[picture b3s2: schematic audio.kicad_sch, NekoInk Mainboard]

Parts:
C705, C706, C707, C708, C709, C719, C720: 470nF; C_0402_1005Metric
C710, C711: 4.7uF; C_0603_1608Metric
C712, C713: 100uF; C_1206_3216Metric
C714, C715, C716, C717, C718: 100nF; C_0402_1005Metric
J701, J702: Conn_01x02; PinHeader_1x02_P2.00mm_Vertical
J703: AudioJack3_SwitchT; PJ-327E
L701, L702: 120R; L_0603_1608Metric
L703, L704, L705, L706: 15uH; L_0603_1608Metric
R703, R704, R705, R706, R707: 22R; R_0402_1005Metric
R708: 100K; R_0402_1005Metric
U701: WM8960; QFN-32-1EP_5x5mm_P0.5mm_EP3.6x3.6mm_ThermalVias

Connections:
/audio/MICBIAS: C715.1, U701.1 (MICBIAS)
GND: C705.2, C706.2, C707.2, C708.2, C709.2, C710.2, C711.2, C714.1, C715.2, C716.1, C717.1, C718.1, J703.S, U701.9 (DGND), U701.20 (SPKGND), U701.24 (SPKGND), U701.27 (VMID), U701.28 (AGND), U701.33 (GND_PADDLE); also elsewhere on the board
I2C1_SCL: U701.17 (SCLK); also elsewhere on the board
I2C1_SDA: U701.18 (SDIN); also elsewhere on the board
unnamed: C706.1, C707.1, C708.1, C711.1, L701.1, U701.10 (DBVDD), U701.21 (SPKVDD), U701.26 (SPKVDD)
unnamed: C709.1, C710.1, L702.1, U701.32 (AVDD)
unnamed: C712.1, U701.31 (HP_L)
unnamed: C712.2, J703.T
unnamed: C713.1, U701.29 (HP_R)
unnamed: C713.2, J703.R
unnamed: C714.2, C720.2, J702.2, L706.2
unnamed: C716.2, C720.1, J702.1, L705.2
unnamed: C717.2, C719.2, J701.2, L704.2
unnamed: C718.2, C719.1, J701.1, L703.2
unnamed: J703.TN, R708.2, U701.7 (RINPUT3)
unnamed: L703.1, U701.25 (SPK_LP)
unnamed: L704.1, U701.23 (SPK_LN)
unnamed: L705.1, U701.22 (SPK_RP)
unnamed: L706.1, U701.19 (SPK_RN)
unnamed: R703.2, U701.13 (DACLRC), U701.15 (ADCLRC)
unnamed: R704.2, U701.12 (BCLK)
unnamed: R705.2, U701.16 (ADCDAT)
unnamed: R706.2, U701.14 (DACDAT)
unnamed: R707.2, U701.11 (MCLK)
SAI2_MCLK: R707.1; also elsewhere on the board
SAI2_RXD: R705.1; also elsewhere on the board
SAI2_TXC: R704.1; also elsewhere on the board
SAI2_TXD: R706.1; also elsewhere on the board
SAI2_TXFS: R703.1; also elsewhere on the board

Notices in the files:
pcb/audio.kicad_sch:
Copyright 2021 Wenting Zhang
This source describes Open Hardware and is licensed under the CERN-OHL-P v2.
pcb/pcb.kicad_pcb:
Copyright EI-2030 2021. / Engineer: Wenting Zhang
This source describes Open Hardware and is licensed under the CERN-OHL-S v2.
